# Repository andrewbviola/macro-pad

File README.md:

# macro-pad
 Experimenting with PCBs

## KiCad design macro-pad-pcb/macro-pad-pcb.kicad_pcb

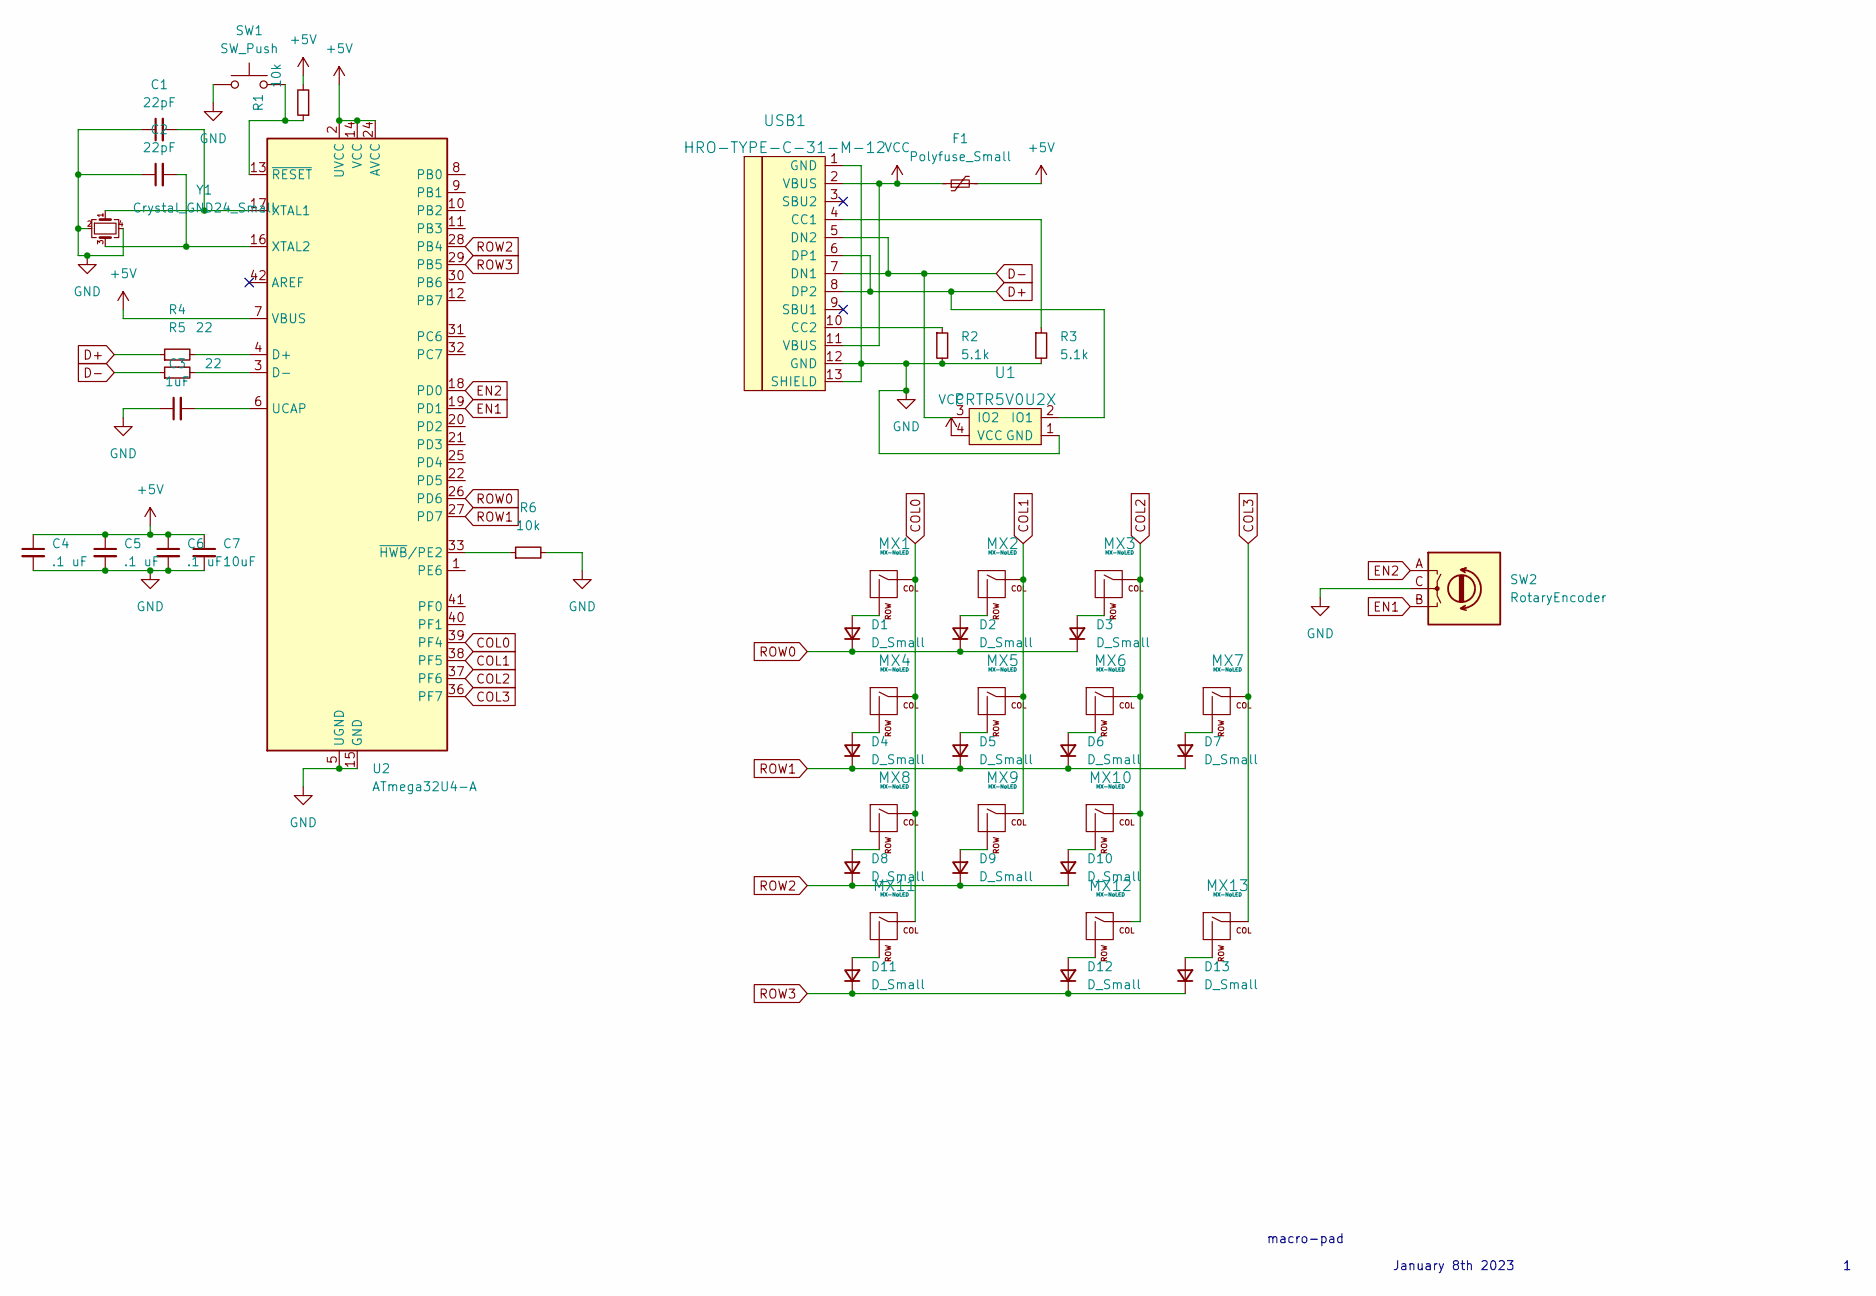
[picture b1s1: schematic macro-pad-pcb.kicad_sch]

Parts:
C1, C2: 22pF; C_0805_2012Metric
C3: 1uF; C_0805_2012Metric
C4, C5, C6: .1 uF; C_0805_2012Metric
C7: 10uF; C_0805_2012Metric
D1, D2, D3, D4, D5, D6, D7, D8, D9, D10, D11, D12, D13: D_Small; D_SOD-123
F1: Polyfuse_Small; Fuse_1206_3216Metric
MX1, MX2, MX3, MX4, MX5, MX6, MX8, MX9, MX10, MX12: MX-NoLED; MX-1U
MX7, MX11, MX13: MX-NoLED; MX-2U
R1, R6: 10k; R_0805_2012Metric
R2, R3: 5.1k; R_0805_2012Metric
R4, R5: 22; R_0805_2012Metric
SW1: SW_Push; SKQG-1155865
SW2: RotaryEncoder; RotaryEncoder_Alps_EC11E-Switch_Vertical_H20mm_CircularMoun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
U1: PRTR5V0U2X; SOT143B
U2: ATmega32U4-A; TQFP-44_10x10mm_P0.8mm
USB1: HRO-TYPE-C-31-M-12; HRO-TYPE-C-31-M-12-HandSoldering
Y1: Crystal_GND24_Small; Crystal_SMD_3225-4Pin_3.2x2.5mm_HandSoldering

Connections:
+5V: C4.1, C5.1, C6.1, C7.1, F1.2, R1.2, U2.2 (UVCC), U2.7 (VBUS), U2.14 (VCC), U2.24 (AVCC), U2.34 (VCC), U2.44 (AVCC)
COL0: MX1.1 (COL), MX4.1 (COL), MX8.1 (COL), MX11.1 (COL), U2.39 (PF4)
COL1: MX2.1 (COL), MX5.1 (COL), MX9.1 (COL), U2.38 (PF5)
COL2: MX3.1 (COL), MX6.1 (COL), MX10.1 (COL), MX12.1 (COL), U2.37 (PF6)
COL3: MX7.1 (COL), MX13.1 (COL), U2.36 (PF7)
D+: R4.1, U1.2 (IO1), USB1.6 (DP1), USB1.8 (DP2)
D-: R5.1, U1.3 (IO2), USB1.5 (DN2), USB1.7 (DN1)
EN1: SW2.B, U2.19 (PD1)
EN2: SW2.A, U2.18 (PD0)
GND: C1.1, C2.1, C3.1, C4.2, C5.2, C6.2, C7.2, R2.2, R3.2, R6.2, SW1.1, SW2.C, U1.1 (GND), U2.5 (UGND), U2.15 (GND), U2.23 (GND), U2.35 (GND), U2.43 (GND), USB1.1 (GND), USB1.12 (GND), USB1.13 (SHIELD), Y1.2, Y1.4
unnamed: C1.2, U2.17 (XTAL1), Y1.1
unnamed: C2.2, U2.16 (XTAL2), Y1.3
unnamed: C3.2, U2.6 (UCAP)
unnamed: D1.2 (A), MX1.2 (ROW)
unnamed: D2.2 (A), MX2.2 (ROW)
unnamed: D3.2 (A), MX3.2 (ROW)
unnamed: D4.2 (A), MX4.2 (ROW)
unnamed: D5.2 (A), MX5.2 (ROW)
unnamed: D6.2 (A), MX6.2 (ROW)
unnamed: D7.2 (A), MX7.2 (ROW)
unnamed: D8.2 (A), MX8.2 (ROW)
unnamed: D9.2 (A), MX9.2 (ROW)
unnamed: D10.2 (A), MX10.2 (ROW)
unnamed: D11.2 (A), MX11.2 (ROW)
unnamed: D12.2 (A), MX12.2 (ROW)
unnamed: D13.2 (A), MX13.2 (ROW)
unnamed: R1.1, SW1.2, U2.13 (~RESET)
unnamed: R2.1, USB1.10 (CC2)
unnamed: R3.1, USB1.4 (CC1)
unnamed: R4.2, U2.4 (D+)
unnamed: R5.2, U2.3 (D-)
unnamed: R6.1, U2.33 (~HWB/PE2)
ROW0: D1.1 (K), D2.1 (K), D3.1 (K), U2.26 (PD6)
ROW1: D4.1 (K), D5.1 (K), D6.1 (K), D7.1 (K), U2.27 (PD7)
ROW2: D8.1 (K), D9.1 (K), D10.1 (K), U2.28 (PB4)
ROW3: D11.1 (K), D12.1 (K), D13.1 (K), U2.29 (PB5)
VCC: F1.1, U1.4 (VCC), USB1.2 (VBUS), USB1.11 (VBUS)

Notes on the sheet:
macro-pad
January 8th 2023

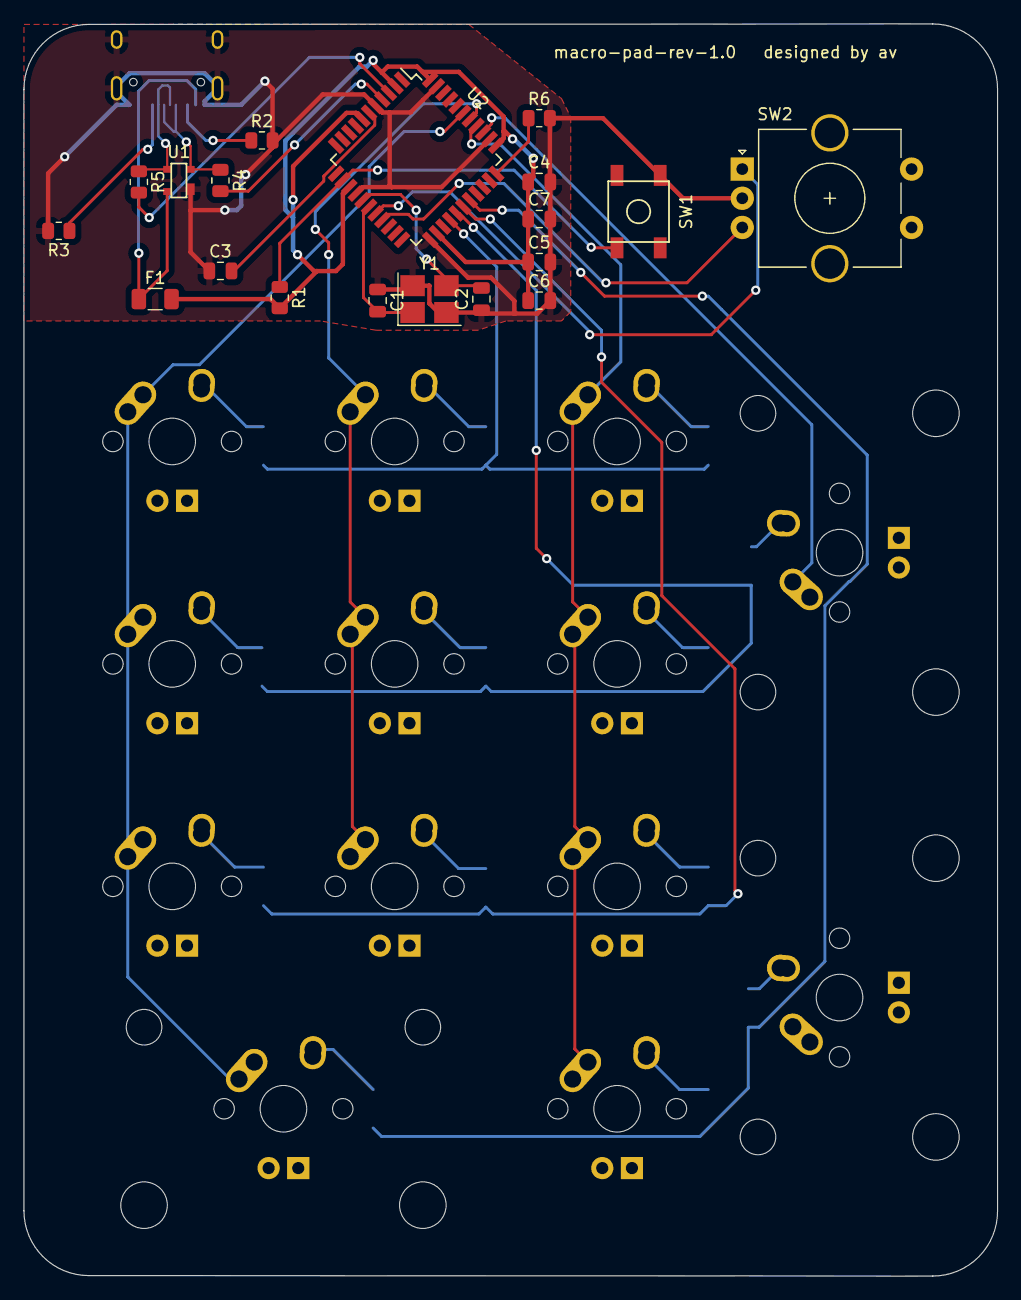
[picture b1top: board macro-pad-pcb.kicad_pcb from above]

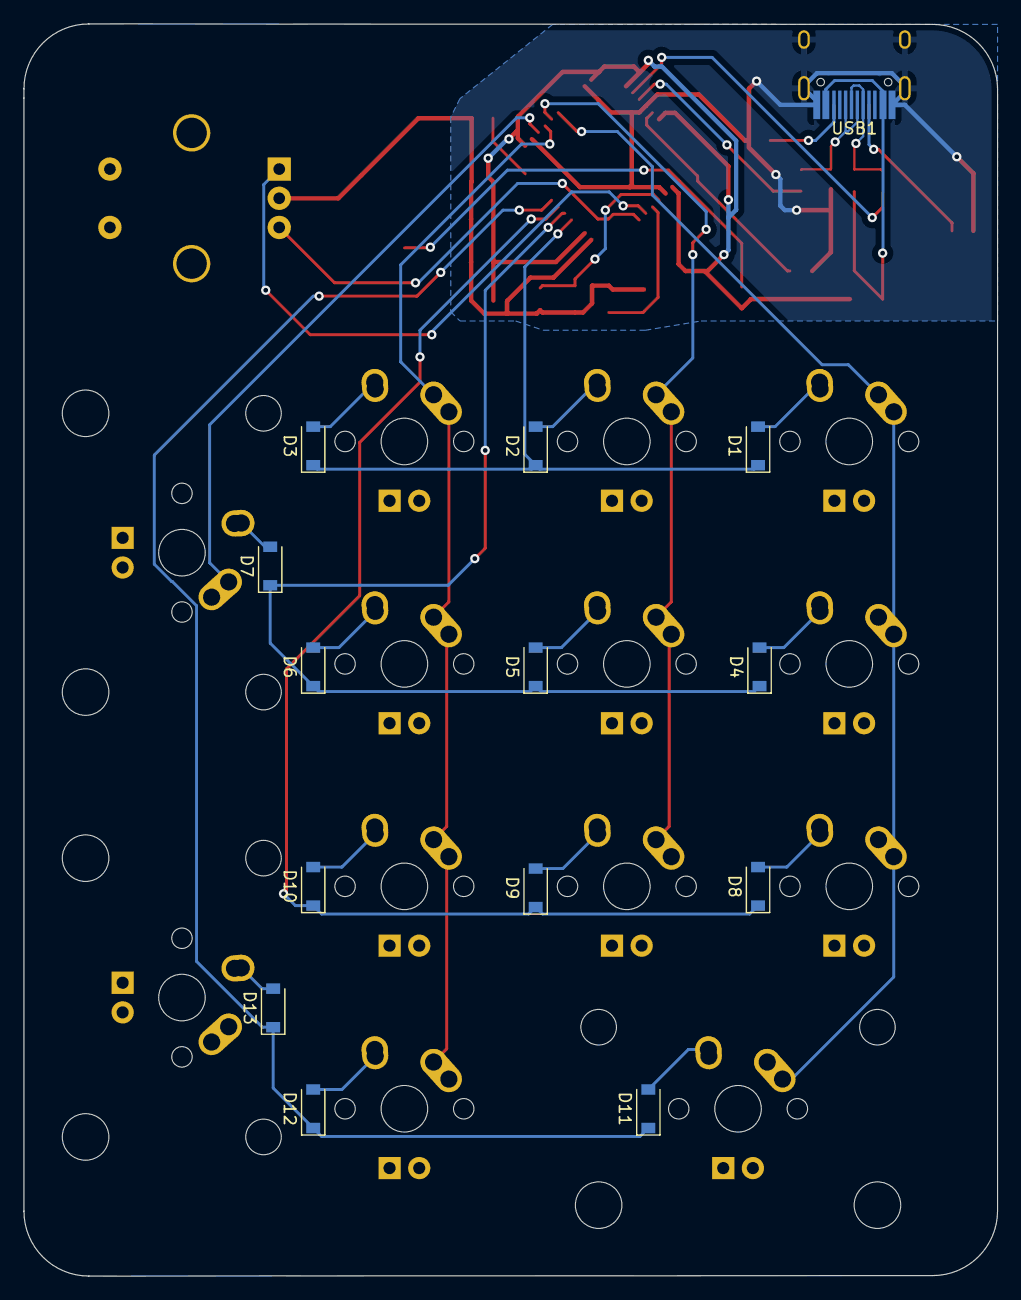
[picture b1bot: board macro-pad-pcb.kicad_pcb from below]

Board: 2 copper layers, 83.4 x 107.2 mm, 46 parts (14 on the bottom side), 37 nets.

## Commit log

2023-01-08 Initialized project
2023-01-08 Fixed files
2023-01-08 Add submodules
2023-01-08 Added libraries
2023-01-09 Schematics done
2023-01-09 Worked on traces
2023-01-09 Finished PCB
2023-01-09 Added gerbers
2023-01-09 Boms added
